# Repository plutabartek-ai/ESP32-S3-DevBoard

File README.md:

# ESP32-S3-DevBoard
Zadanie rekrutacyjne - projekt płytki PCB dla modułu ESP32-S3

Projekt kompletnej płytki rozwojowej opartej na układzie **ESP32-S3**, wykonany w ramach zadania rekrutacyjnego.

##  Kluczowe funkcjonalności
* **MCU:** ESP32-S3-WROOM (Wi-Fi + BLE)
* **Zasilanie i Komunikacja:** Port USB-C z układem LDO 3.3V.
* **Interakcja:** Przyciski BOOT i RESET, dioda LED statusowa.
* **Sensory:** Zintegrowany akcelerometr i żyroskop BMI270.

##  Struktura repozytorium
* `/Project_Files` - Pliki źródłowe KiCad (.kicad_sch, .kicad_pcb)
* `/Production` - Pliki Gerber i BOM przygotowane do zamówienia.
* `/step` - Model płytki w formacie .STEP.

##  Wizualizacja projektu
# Schemat ideowy 
# Widok PCB 
# Model 3D

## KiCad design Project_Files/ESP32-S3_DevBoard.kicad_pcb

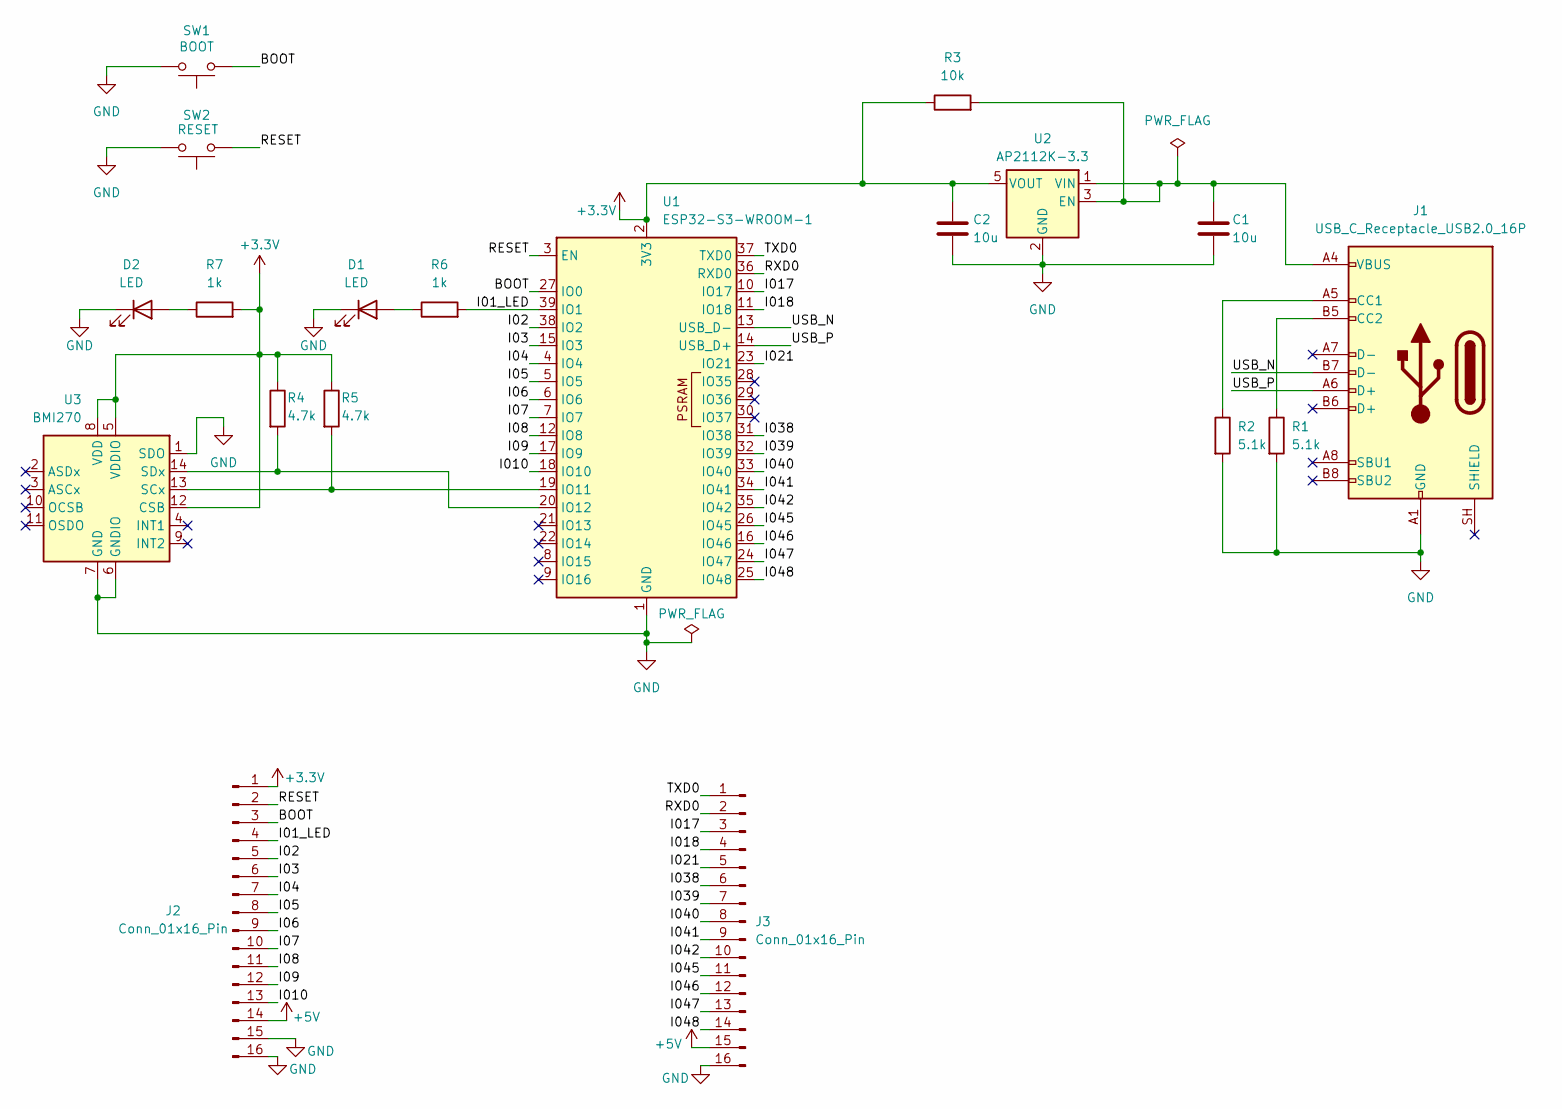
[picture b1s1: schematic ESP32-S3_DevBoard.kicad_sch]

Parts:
C1, C2: 10u; C_0603_1608Metric
D1, D2: LED; LED_0603_1608Metric
J1: USB_C_Receptacle_USB2.0_16P; USB_C_Receptacle_HRO_TYPE-C-31-M-12
J2, J3: Conn_01x16_Pin; PinHeader_1x16_P2.54mm_Vertical
R1, R2: 5.1k; R_0603_1608Metric
R3: 10k; R_0603_1608Metric
R4, R5: 4.7k; R_0603_1608Metric
R6, R7: 1k; R_0603_1608Metric
SW1: BOOT; SW_Push_1TS009xxxx-xxxx-xxxx_6x6x5mm
SW2: RESET; SW_Push_1TS009xxxx-xxxx-xxxx_6x6x5mm
U1: ESP32-S3-WROOM-1
U2: AP2112K-3.3; SOT-23-5
U3: BMI270; Bosch_LGA-14_3x2.5mm_P0.5mm

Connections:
+3.3V: C2.1, J2.1, R3.1, R4.1, R5.1, R7.2, U1.2 (3V3), U2.5 (VOUT), U3.5 (VDDIO), U3.8 (VDD), U3.12 (CSB)
+5V: J2.14, J3.15
/BOOT: J2.3, SW1.2, U1.27 (IO0)
/I01_LED: J2.4, R6.2, U1.39 (IO1)
/I02: J2.5, U1.38 (IO2)
/I03: J2.6, U1.15 (IO3)
/I04: J2.7, U1.4 (IO4)
/I05: J2.8, U1.5 (IO5)
/I06: J2.9, U1.6 (IO6)
/I07: J2.10, U1.7 (IO7)
/I08: J2.11, U1.12 (IO8)
/I09: J2.12, U1.17 (IO9)
/I010: J2.13, U1.18 (IO10)
/I017: J3.3, U1.10 (IO17)
/I018: J3.4, U1.11 (IO18)
/I021: J3.5, U1.23 (IO21)
/I038: J3.6, U1.31 (IO38)
/I039: J3.7, U1.32 (IO39)
/I040: J3.8, U1.33 (IO40)
/I041: J3.9, U1.34 (IO41)
/I042: J3.10, U1.35 (IO42)
/I045: J3.11, U1.26 (IO45)
/I046: J3.12, U1.16 (IO46)
/I047: J3.13, U1.24 (IO47)
/I048: J3.14, U1.25 (IO48)
/RESET: J2.2, SW2.1, U1.3 (EN)
/RXD0: J3.2, U1.36 (RXD0)
/TXD0: J3.1, U1.37 (TXD0)
/USB_N: J1.B7 (D-), U1.13 (USB_D-)
/USB_P: J1.A6 (D+), U1.14 (USB_D+)
GND: C1.2, C2.2, D1.1 (K), D2.1 (K), J1.A1 (GND), J1.A12 (GND), J1.B1 (GND), J1.B12 (GND), J2.15, J2.16, J3.16, R1.2, R2.2, SW1.1, SW2.2, U1.1 (GND), U1.40 (GND), U1.41 (GND), U2.2 (GND), U3.1 (SDO), U3.6 (GNDIO), U3.7 (GND)
unnamed: D1.2 (A), R6.1
unnamed: D2.2 (A), R7.1
unnamed: J1.A5 (CC1), R2.1
unnamed: J1.B5 (CC2), R1.1
unnamed: R5.2, U1.19 (IO11), U3.13 (SCx)
unnamed: R4.2, U1.20 (IO12), U3.14 (SDx)
unnamed: C1.1, J1.A4 (VBUS), J1.A9 (VBUS), J1.B4 (VBUS), J1.B9 (VBUS), R3.2, U2.1 (VIN), U2.3 (EN)

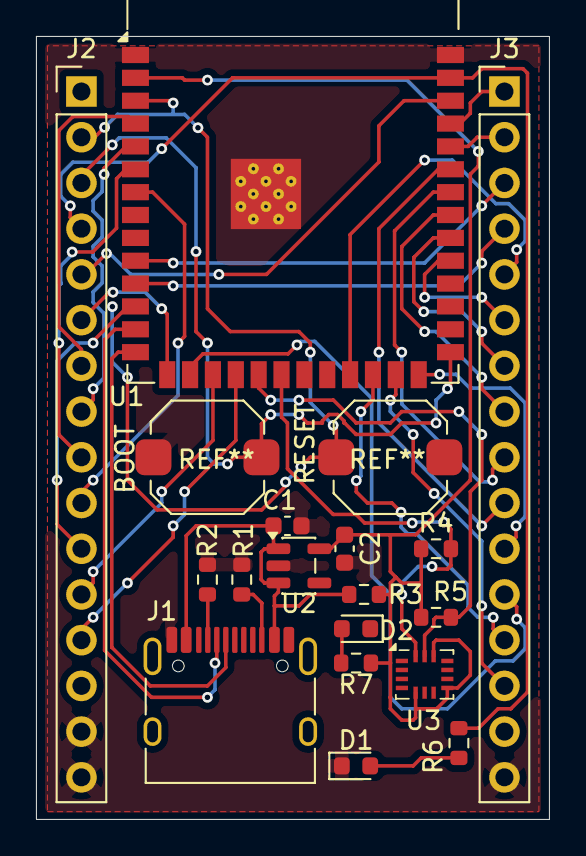
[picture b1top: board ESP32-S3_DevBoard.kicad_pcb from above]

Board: 2 copper layers, 28.5 x 43.5 mm, 19 parts (0 on the bottom side), 38 nets.

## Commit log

2026-04-03 Enhance README with project details and visuals
    Added detailed project description, key features, repository structure, and visualizations.
